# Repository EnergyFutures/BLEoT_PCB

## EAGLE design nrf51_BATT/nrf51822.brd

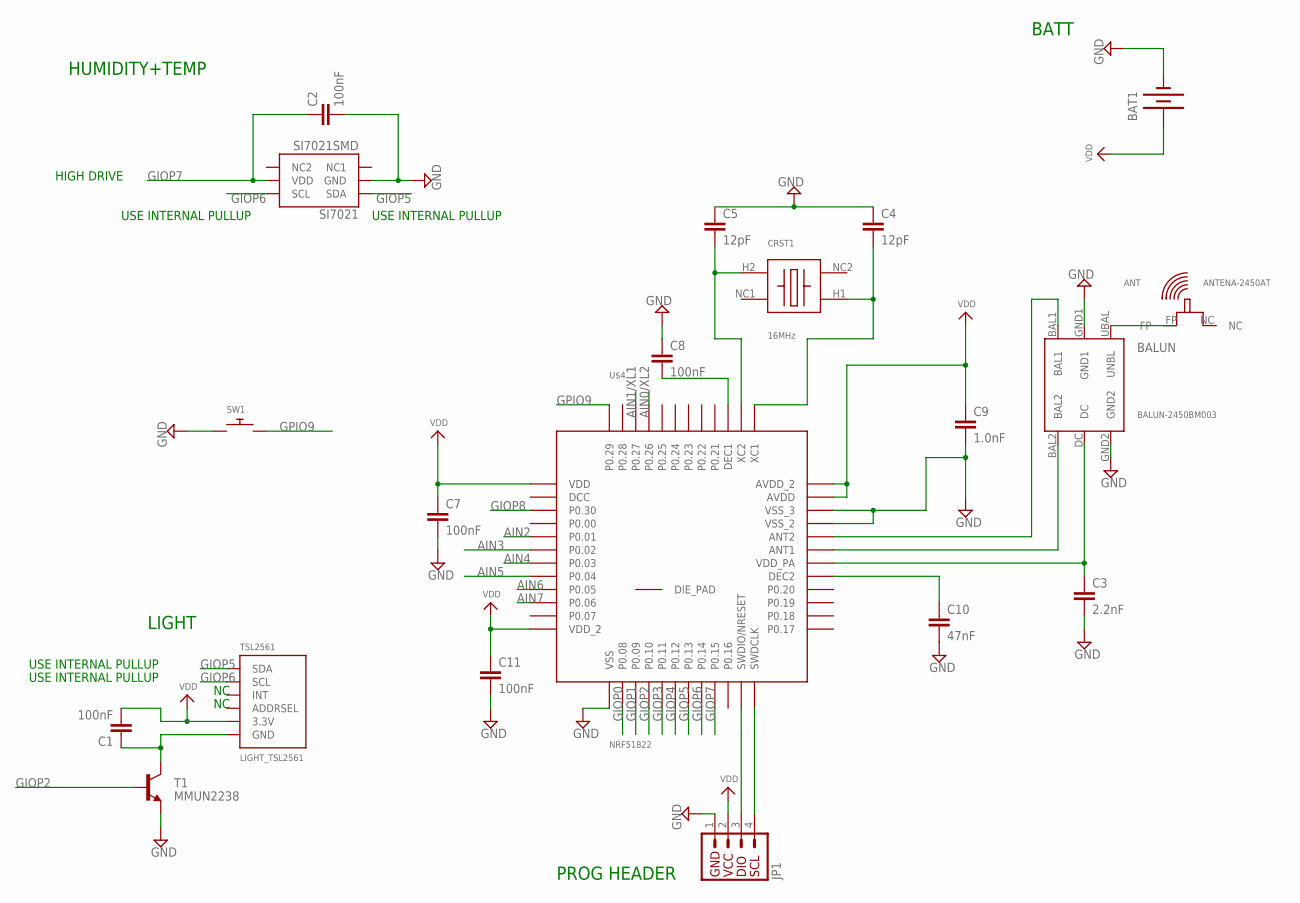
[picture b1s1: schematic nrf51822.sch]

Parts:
ANT: ANTENA-2450AT; 2450AT18B100
BALUN: BALUN-2450BM003; 2450BM14E0003
BAT1: BATTERY245PTH; BATTCON_245MM_PTH
C1, C2, C7, C8, C11: 100nF; C0805
C3: 2.2nF; C0805
C4, C5: 12pF; C0805
C9: 1.0nF; C0805
C10: 47nF; C0805
CRST1: 16MHz; CRYSTAL16MHZ
JP1: PROG_HEADER; 1X04
SI7021: SI7021SMD; SI7021
SW1: SWITCH_PUSHBUTTONSOFTTOUCHSMD_SJ; PUSHBUTTON_SMD_SJ
T1: MMUN2238; SOT23-3
TSL2561: LIGHT_TSL2561; TSL2561_FN
U$4: NRF51822; QFN48

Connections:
AIN0/XL2: U$4.45 (P0.26)
AIN1/XL1: U$4.46 (P0.27)
AIN2: U$4.5 (P0.01)
AIN3: U$4.6 (P0.02)
AIN4: U$4.7 (P0.03)
AIN5: U$4.8 (P0.04)
AIN6: U$4.9 (P0.05)
AIN7: U$4.10 (P0.06)
GIOP0: U$4.14 (P0.08)
GIOP1: U$4.15 (P0.09)
GIOP2: T1.1 (B), U$4.16 (P0.10)
GIOP3: U$4.17 (P0.11)
GIOP4: U$4.18 (P0.12)
GIOP5: SI7021.1 (SDA), TSL2561.DATA (SDA), U$4.19 (P0.13)
GIOP6: SI7021.6 (SCL), TSL2561.CLK (SCL), U$4.20 (P0.14)
GIOP7: C2.1, SI7021.5 (VDD), U$4.21 (P0.15)
GIOP8: U$4.3 (P0.30)
GND: BALUN.GND1, BALUN.GND2, BAT1.2 (-), C2.2, C3.2, C4.1, C5.1, C7.2, C8.1, C9.2, C10.2, C11.2, JP1.1, SI7021.2 (GND), SW1.P$1, T1.2 (E), U$4.13 (VSS), U$4.33 (VSS_2), U$4.34 (VSS_3)
GPIO9: SW1.P$2, U$4.48 (P0.29)
unnamed: C5.2, CRST1.H2, U$4.38 (XC2)
unnamed: C4.2, CRST1.H1, U$4.37 (XC1)
unnamed: ANT.FP, BALUN.UBAL (UNBL)
unnamed: BALUN.DC, C3.1, U$4.30 (VDD_PA)
unnamed: C8.2, U$4.39 (DEC1)
unnamed: BALUN.BAL1, U$4.32 (ANT2)
unnamed: C1.1, T1.3 (C), TSL2561.VSS (GND)
unnamed: JP1.3, U$4.23 (SWDIO/NRESET)
unnamed: BALUN.BAL2, U$4.31 (ANT1)
unnamed: C10.1, U$4.29 (DEC2)
unnamed: JP1.4, U$4.24 (SWDCLK)
VDD: BAT1.1 (+), BAT1.3 (+), C1.2, C7.1, C9.1, C11.1, JP1.2, TSL2561.VDD (3.3V), U$4.1 (VDD), U$4.12 (VDD_2), U$4.35 (AVDD), U$4.36 (AVDD_2)

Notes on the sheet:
USE INTERNAL PULLUP
LIGHT
BATT
HIGH DRIVE
HUMIDITY+TEMP
PROG HEADER

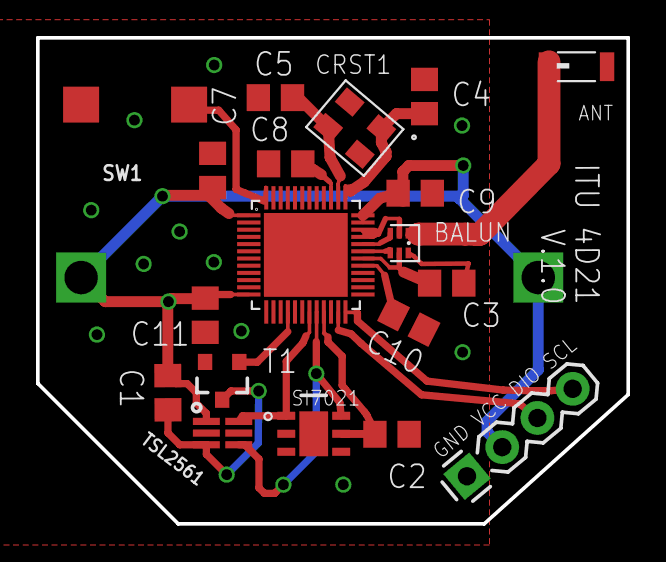
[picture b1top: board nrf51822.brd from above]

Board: 2 copper layers, 32.8 x 27.0 mm, 20 parts (1 on the bottom side), 18 nets.

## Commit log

2015-03-12 init.. v.1.1 with BNT + HD + P + T + TH + L
2015-03-12 Init.. v.0
2015-03-14 Sensor board should be 100% done... Waiting for boards from slow china :0)
2015-03-15 Done with routing.. should be more or less done
2015-03-15 This contains all devices used in both projects
2015-03-16 CLEANED AND ADDED COMMENTS / TAGS ACTUATION MADE 45% SMALLER
2015-03-17 Added optional low pass filter circut and cleaned up some more
2015-03-22 Small changes
2015-03-26 Added a TMP36 sensor to ensure a power cutoff if the temperature rises above a threshold (in case of fire or shortcut)
2015-03-26 Version 1.2 of the sensor board. Removed the motion sensor (v1.1 will have it) Removed TMP36... no need for it as we are going to use the digital H+T Connected both I2C components to the same lines (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
2015-03-28 Cleaned sensor board v.1.2 - TAG AS SENT TO SMART PROTOTYPE Cleaned actuation board v.1.0 - TAG AS SENT TO SMART PROTOTYPE Made a compact version of the sensor board - TAG AS SENT TO SMART PROTOTYPE
2015-04-07 Sent to smart-prototype Actuation 1.2 Compact 1.1

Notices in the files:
parts and their libraries:
microbuilder: This work is placed in the public domain, and may be freely used for commercial and non-commercial work with the following conditions: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
SparkFun-DiscreteSemi: Licensing: Creative Commons ShareAlike 4.0 International - https://creativecommons.org/licenses/by-sa/4.0
